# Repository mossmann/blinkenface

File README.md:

# blinkenface
party glasses with blinky lights

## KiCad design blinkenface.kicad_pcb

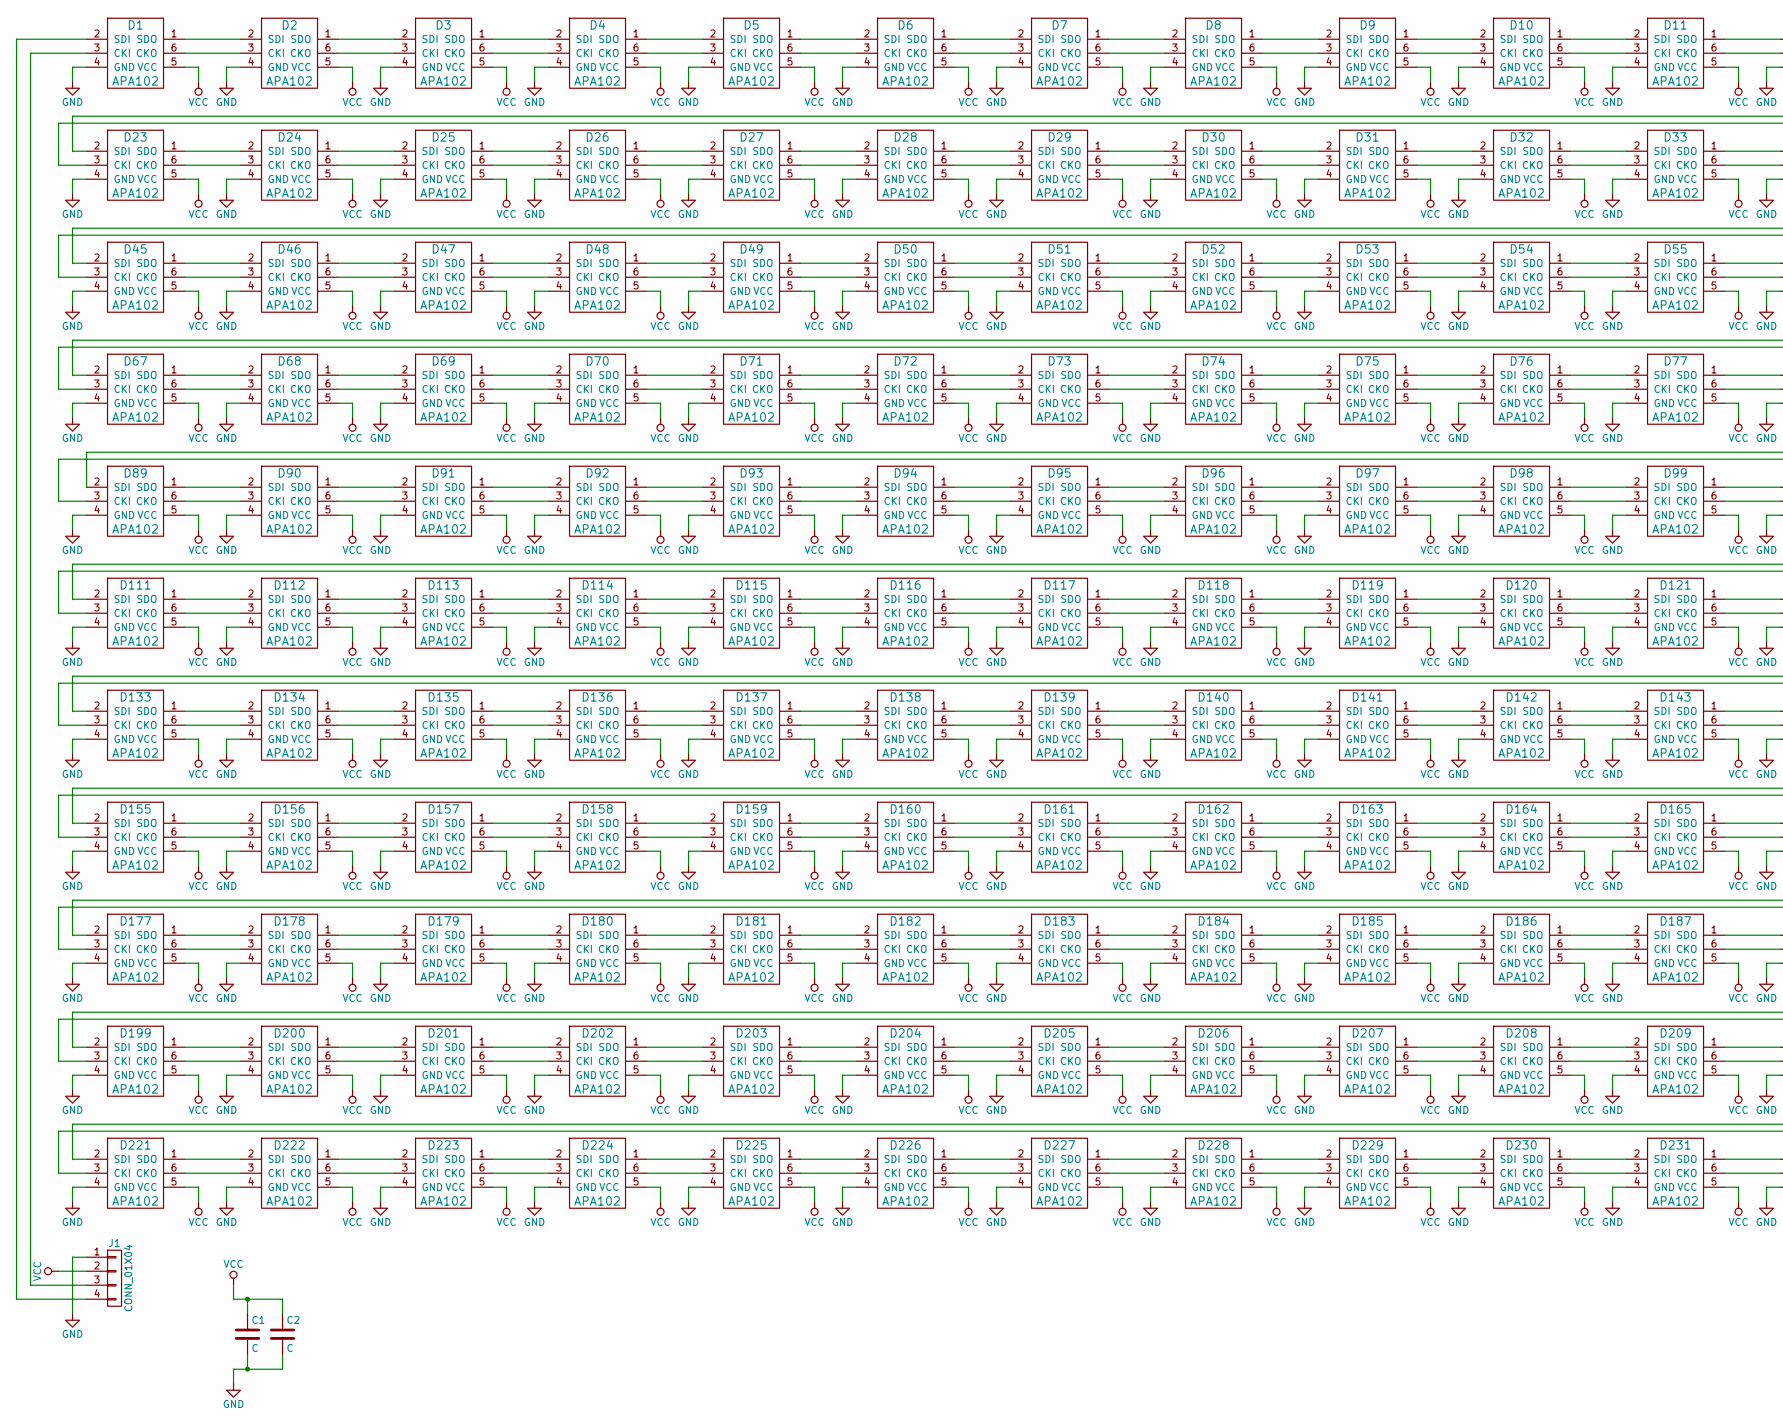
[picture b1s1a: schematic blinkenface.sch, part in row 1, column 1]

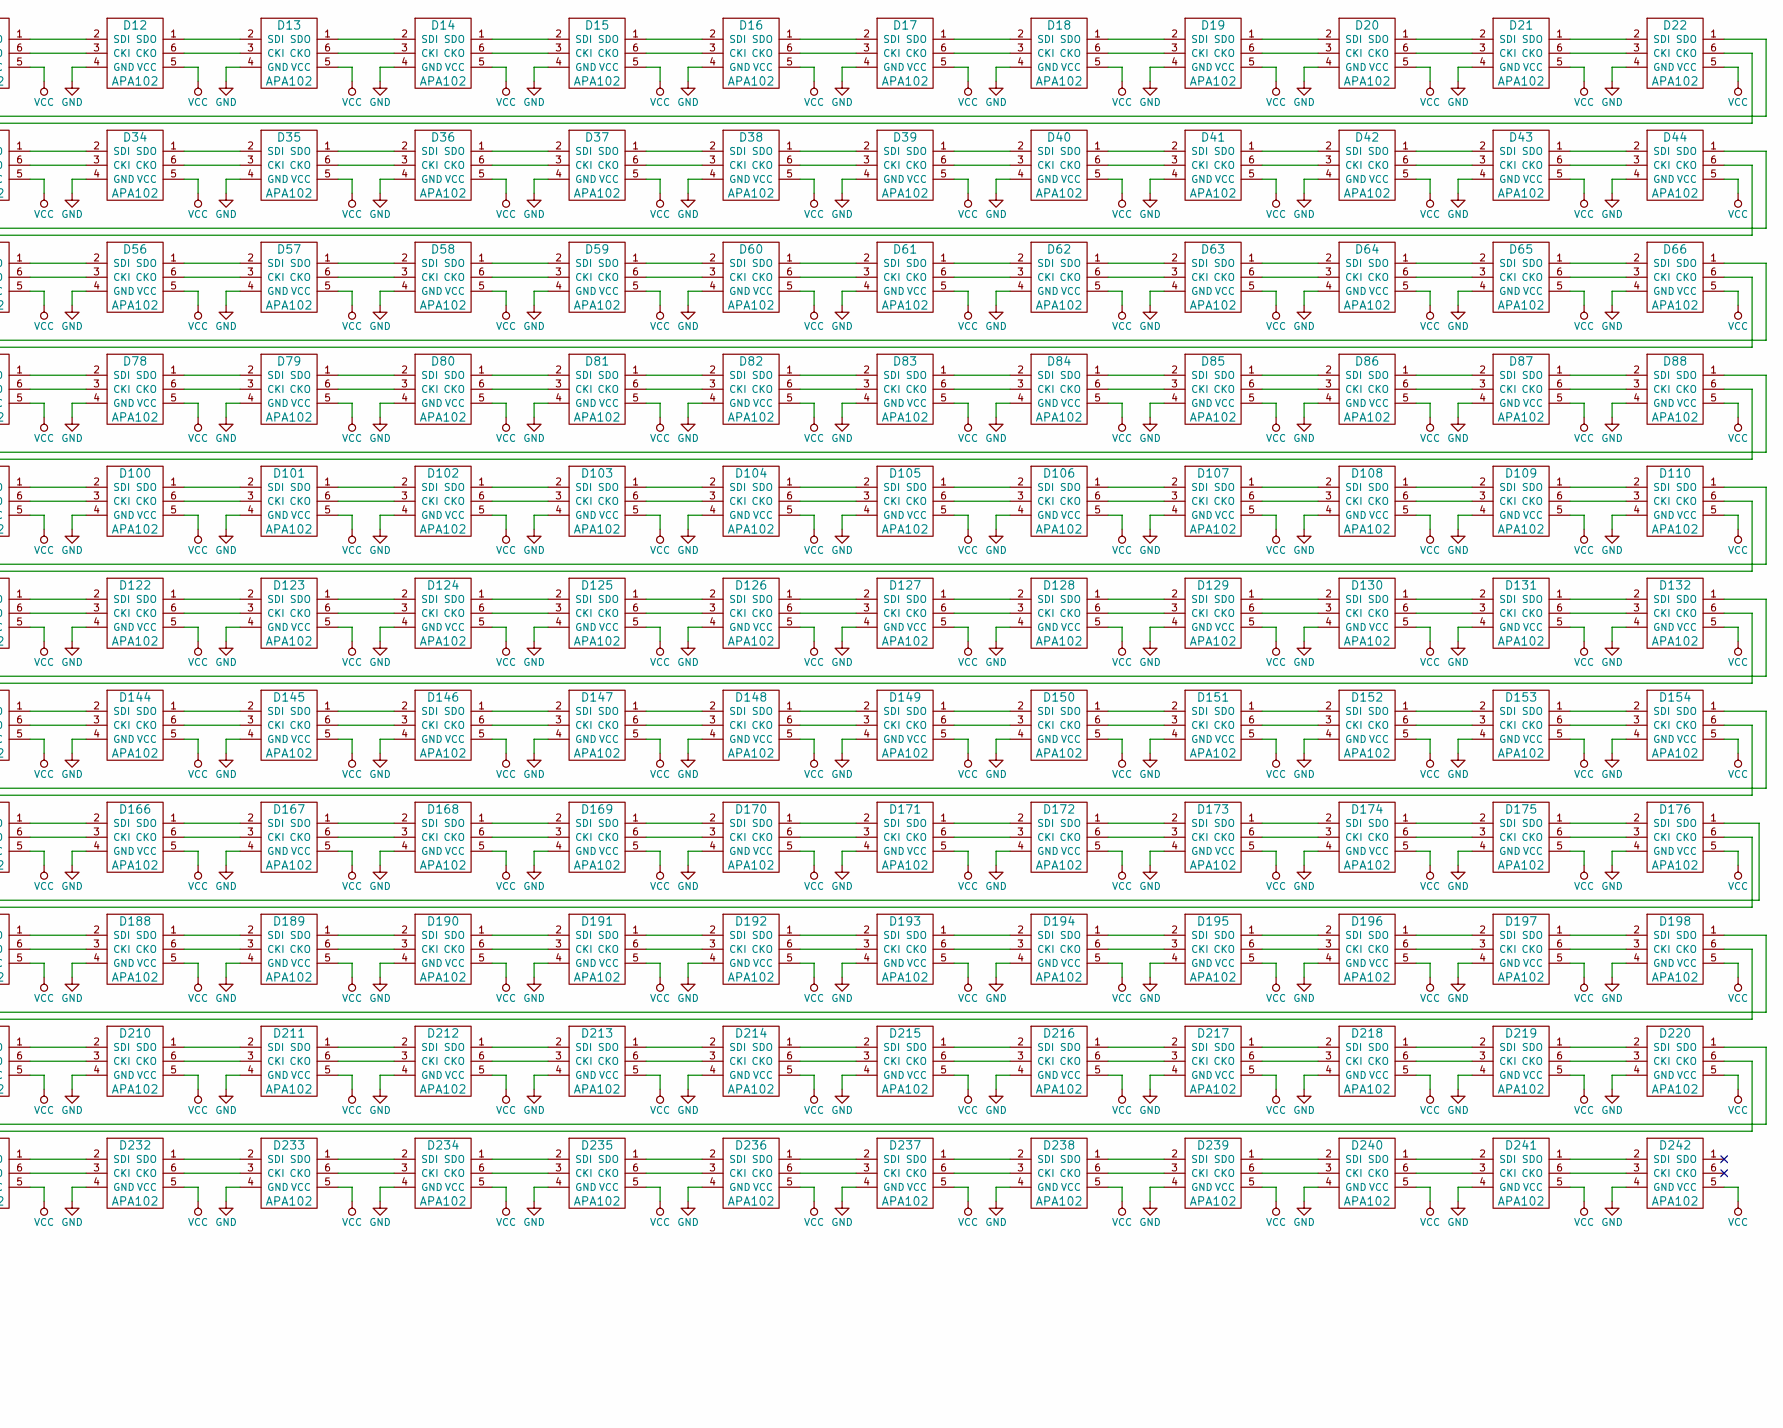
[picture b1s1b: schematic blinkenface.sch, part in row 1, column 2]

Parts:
C1: C; 0805
C2: C; 0603
D1, D2, D3, D4, D5, D6, D7, D8, D9, D10, D11, D12, D13, D14, D15, D16, D17, D18, D19, D20, D21, D22, D23, D24, D25, D26, D27, D28, D29, D30, D31, D32, D33, D34, D35, D36, D37, D38, D39, D40, D41, D42, D43, D44, D45, D46, D47, D48, D49, D50, D51, D52, D53, D54, D55, D56, D57, D58, D59, D60, D61, D62, D63, D64, D65, D66, D67, D68, D69, D70, D71, D72, D73, D74, D75, D76, D77, D78, D79, D80, D81, D82, D83, D84, D85, D86, D87, D88, D89, D90, D91, D92, D93, D94, D95, D96, D97, D98, D99, D100, D101, D102, D103, D104, D105, D106, D107, D108, D109, D110, D111, D112, D113, D114, D115, D116, D117, D118, D119, D120, D121, D122, D123, D124, D125, D126, D127, D128, D129, D130, D131, D132, D133, D134, D135, D136, D137, D138, D139, D140, D141, D142, D143, D144, D145, D146, D147, D148, D149, D150, D151, D152, D153, D154, D155, D156, D157, D158, D159, D160, D161, D162, D163, D164, D165, D166, D167, D168, D169, D170, D171, D172, D173, D174, D175, D176, D177, D178, D179, D180, D181, D182, D183, D184, D185, D186, D187, D188, D189, D190, D191, D192, D193, D194, D195, D196, D197, D198, D199, D200, D201, D202, D203, D204, D205, D206, D207, D208, D209, D210, D211, D212, D213, D214, D215, D216, D217, D218, D219, D220, D221, D222, D223, D224, D225, D226, D227, D228, D229, D230, D231, D232, D233, D234, D235, D236, D237, D238, D239, D240, D241, D242: APA102; APA102-2020
J1: CONN_01X04; HEADER-1x4

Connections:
GND: C1.2, C2.2, D1.4 (GND), D2.4 (GND), D3.4 (GND), D4.4 (GND), D5.4 (GND), D6.4 (GND), D7.4 (GND), D8.4 (GND), D9.4 (GND), D10.4 (GND), D11.4 (GND), D12.4 (GND), D13.4 (GND), D14.4 (GND), D15.4 (GND), D16.4 (GND), D17.4 (GND), D18.4 (GND), D19.4 (GND), D20.4 (GND), D21.4 (GND), D22.4 (GND), D23.4 (GND), D24.4 (GND), D25.4 (GND), D26.4 (GND), D27.4 (GND), D28.4 (GND), D29.4 (GND), D30.4 (GND), D31.4 (GND), D32.4 (GND), D33.4 (GND), D34.4 (GND), D35.4 (GND), D36.4 (GND), D37.4 (GND), D38.4 (GND), D39.4 (GND), D40.4 (GND), D41.4 (GND), D42.4 (GND), D43.4 (GND), D44.4 (GND), D45.4 (GND), D46.4 (GND), D47.4 (GND), D48.4 (GND), D49.4 (GND), D50.4 (GND), D51.4 (GND), D52.4 (GND), D53.4 (GND), D54.4 (GND), D55.4 (GND), D56.4 (GND), D57.4 (GND), D58.4 (GND), D59.4 (GND), D60.4 (GND), D61.4 (GND), D62.4 (GND), D63.4 (GND), D64.4 (GND), D65.4 (GND), D66.4 (GND), D67.4 (GND), D68.4 (GND), D69.4 (GND), D70.4 (GND), D71.4 (GND), D72.4 (GND), D73.4 (GND), D74.4 (GND), D75.4 (GND), D76.4 (GND), D77.4 (GND), D78.4 (GND), D79.4 (GND), D80.4 (GND), D81.4 (GND), D82.4 (GND), D83.4 (GND), D84.4 (GND), D85.4 (GND), D86.4 (GND), D87.4 (GND), D88.4 (GND), D89.4 (GND), D90.4 (GND), D91.4 (GND), D92.4 (GND), D93.4 (GND), D94.4 (GND), D95.4 (GND), D96.4 (GND), D97.4 (GND), D98.4 (GND), D99.4 (GND), D100.4 (GND), D101.4 (GND), D102.4 (GND), D103.4 (GND), D104.4 (GND), D105.4 (GND), D106.4 (GND), D107.4 (GND), D108.4 (GND), D109.4 (GND), D110.4 (GND), D111.4 (GND), D112.4 (GND), D113.4 (GND), D114.4 (GND), D115.4 (GND), D116.4 (GND), D117.4 (GND), D118.4 (GND), D119.4 (GND), D120.4 (GND), D121.4 (GND), D122.4 (GND), D123.4 (GND), D124.4 (GND), D125.4 (GND), D126.4 (GND), D127.4 (GND), D128.4 (GND), D129.4 (GND), D130.4 (GND), D131.4 (GND), D132.4 (GND), D133.4 (GND), D134.4 (GND), D135.4 (GND), D136.4 (GND), D137.4 (GND), D138.4 (GND), D139.4 (GND), D140.4 (GND), D141.4 (GND), D142.4 (GND), D143.4 (GND), D144.4 (GND), D145.4 (GND), D146.4 (GND), D147.4 (GND), D148.4 (GND), D149.4 (GND), D150.4 (GND), D151.4 (GND), D152.4 (GND), D153.4 (GND), D154.4 (GND), D155.4 (GND), D156.4 (GND), D157.4 (GND), D158.4 (GND), D159.4 (GND), D160.4 (GND), D161.4 (GND), D162.4 (GND), D163.4 (GND), D164.4 (GND), D165.4 (GND), D166.4 (GND), D167.4 (GND), D168.4 (GND), D169.4 (GND), D170.4 (GND), D171.4 (GND), D172.4 (GND), D173.4 (GND), D174.4 (GND), D175.4 (GND), D176.4 (GND), D177.4 (GND), D178.4 (GND), D179.4 (GND), D180.4 (GND), D181.4 (GND), D182.4 (GND), D183.4 (GND), D184.4 (GND), D185.4 (GND), D186.4 (GND), D187.4 (GND), D188.4 (GND), D189.4 (GND), D190.4 (GND), D191.4 (GND), D192.4 (GND), D193.4 (GND), D194.4 (GND), D195.4 (GND), D196.4 (GND), D197.4 (GND), D198.4 (GND), D199.4 (GND), D200.4 (GND), D201.4 (GND), D202.4 (GND), D203.4 (GND), D204.4 (GND), D205.4 (GND), D206.4 (GND), D207.4 (GND), D208.4 (GND), D209.4 (GND), D210.4 (GND), D211.4 (GND), D212.4 (GND), D213.4 (GND), D214.4 (GND), D215.4 (GND), D216.4 (GND), D217.4 (GND), D218.4 (GND), D219.4 (GND), D220.4 (GND), D221.4 (GND), D222.4 (GND), D223.4 (GND), D224.4 (GND), D225.4 (GND), D226.4 (GND), D227.4 (GND), D228.4 (GND), D229.4 (GND), D230.4 (GND), D231.4 (GND), D232.4 (GND), D233.4 (GND), D234.4 (GND), D235.4 (GND), D236.4 (GND), D237.4 (GND), D238.4 (GND), D239.4 (GND), D240.4 (GND), D241.4 (GND), D242.4 (GND), J1.1
unnamed: D1.1 (SDO), D2.2 (SDI)
unnamed: D1.2 (SDI), J1.4
unnamed: D1.3 (CKI), J1.3
unnamed: D1.6 (CKO), D2.3 (CKI)
unnamed: D2.1 (SDO), D3.2 (SDI)
unnamed: D2.6 (CKO), D3.3 (CKI)
unnamed: D3.1 (SDO), D4.2 (SDI)
unnamed: D3.6 (CKO), D4.3 (CKI)
unnamed: D4.1 (SDO), D5.2 (SDI)
unnamed: D4.6 (CKO), D5.3 (CKI)
unnamed: D5.1 (SDO), D6.2 (SDI)
unnamed: D5.6 (CKO), D6.3 (CKI)
unnamed: D6.1 (SDO), D7.2 (SDI)
unnamed: D6.6 (CKO), D7.3 (CKI)
unnamed: D7.1 (SDO), D8.2 (SDI)
unnamed: D7.6 (CKO), D8.3 (CKI)
unnamed: D8.1 (SDO), D9.2 (SDI)
unnamed: D8.6 (CKO), D9.3 (CKI)
unnamed: D10.1 (SDO), D11.2 (SDI)
unnamed: D9.1 (SDO), D10.2 (SDI)
unnamed: D9.6 (CKO), D10.3 (CKI)
unnamed: D10.6 (CKO), D11.3 (CKI)
unnamed: D11.1 (SDO), D12.2 (SDI)
unnamed: D11.6 (CKO), D12.3 (CKI)
unnamed: D12.1 (SDO), D13.2 (SDI)
unnamed: D12.6 (CKO), D13.3 (CKI)
unnamed: D13.1 (SDO), D14.2 (SDI)
unnamed: D13.6 (CKO), D14.3 (CKI)
unnamed: D14.1 (SDO), D15.2 (SDI)
unnamed: D14.6 (CKO), D15.3 (CKI)
unnamed: D15.1 (SDO), D16.2 (SDI)
unnamed: D15.6 (CKO), D16.3 (CKI)
unnamed: D16.1 (SDO), D17.2 (SDI)
unnamed: D16.6 (CKO), D17.3 (CKI)
unnamed: D17.1 (SDO), D18.2 (SDI)
unnamed: D17.6 (CKO), D18.3 (CKI)
unnamed: D18.1 (SDO), D19.2 (SDI)
unnamed: D18.6 (CKO), D19.3 (CKI)
unnamed: D19.1 (SDO), D20.2 (SDI)
unnamed: D19.6 (CKO), D20.3 (CKI)
unnamed: D20.1 (SDO), D21.2 (SDI)
unnamed: D20.6 (CKO), D21.3 (CKI)
unnamed: D21.1 (SDO), D22.2 (SDI)
unnamed: D21.6 (CKO), D22.3 (CKI)
unnamed: D22.1 (SDO), D23.2 (SDI)
unnamed: D22.6 (CKO), D23.3 (CKI)
unnamed: D23.1 (SDO), D24.2 (SDI)
unnamed: D23.6 (CKO), D24.3 (CKI)
unnamed: D24.1 (SDO), D25.2 (SDI)
unnamed: D24.6 (CKO), D25.3 (CKI)
unnamed: D25.1 (SDO), D26.2 (SDI)
unnamed: D25.6 (CKO), D26.3 (CKI)
unnamed: D26.1 (SDO), D27.2 (SDI)
unnamed: D26.6 (CKO), D27.3 (CKI)
unnamed: D27.1 (SDO), D28.2 (SDI)
unnamed: D27.6 (CKO), D28.3 (CKI)
unnamed: D28.1 (SDO), D29.2 (SDI)
unnamed: D28.6 (CKO), D29.3 (CKI)
unnamed: D29.1 (SDO), D30.2 (SDI)
unnamed: D29.6 (CKO), D30.3 (CKI)
unnamed: D30.1 (SDO), D31.2 (SDI)
unnamed: D30.6 (CKO), D31.3 (CKI)
unnamed: D31.1 (SDO), D32.2 (SDI)
unnamed: D31.6 (CKO), D32.3 (CKI)
unnamed: D32.1 (SDO), D33.2 (SDI)
unnamed: D32.6 (CKO), D33.3 (CKI)
unnamed: D33.1 (SDO), D34.2 (SDI)
unnamed: D33.6 (CKO), D34.3 (CKI)
unnamed: D34.1 (SDO), D35.2 (SDI)
unnamed: D34.6 (CKO), D35.3 (CKI)
unnamed: D35.1 (SDO), D36.2 (SDI)
unnamed: D35.6 (CKO), D36.3 (CKI)
unnamed: D36.1 (SDO), D37.2 (SDI)
unnamed: D36.6 (CKO), D37.3 (CKI)
unnamed: D37.1 (SDO), D38.2 (SDI)
unnamed: D37.6 (CKO), D38.3 (CKI)
unnamed: D38.1 (SDO), D39.2 (SDI)
unnamed: D38.6 (CKO), D39.3 (CKI)
unnamed: D39.1 (SDO), D40.2 (SDI)
unnamed: D39.6 (CKO), D40.3 (CKI)
unnamed: D40.1 (SDO), D41.2 (SDI)
unnamed: D40.6 (CKO), D41.3 (CKI)
unnamed: D41.1 (SDO), D42.2 (SDI)
unnamed: D41.6 (CKO), D42.3 (CKI)
unnamed: D42.1 (SDO), D43.2 (SDI)
unnamed: D42.6 (CKO), D43.3 (CKI)
unnamed: D43.1 (SDO), D44.2 (SDI)
unnamed: D43.6 (CKO), D44.3 (CKI)
unnamed: D44.1 (SDO), D45.2 (SDI)
unnamed: D44.6 (CKO), D45.3 (CKI)
unnamed: D45.1 (SDO), D46.2 (SDI)
unnamed: D45.6 (CKO), D46.3 (CKI)
unnamed: D46.1 (SDO), D47.2 (SDI)
unnamed: D46.6 (CKO), D47.3 (CKI)
unnamed: D47.1 (SDO), D48.2 (SDI)
unnamed: D47.6 (CKO), D48.3 (CKI)
unnamed: D48.1 (SDO), D49.2 (SDI)
unnamed: D48.6 (CKO), D49.3 (CKI)
unnamed: D49.1 (SDO), D50.2 (SDI)
unnamed: D49.6 (CKO), D50.3 (CKI)
unnamed: D50.1 (SDO), D51.2 (SDI)
unnamed: D50.6 (CKO), D51.3 (CKI)
unnamed: D51.1 (SDO), D52.2 (SDI)
unnamed: D51.6 (CKO), D52.3 (CKI)
unnamed: D52.1 (SDO), D53.2 (SDI)
unnamed: D52.6 (CKO), D53.3 (CKI)
unnamed: D53.1 (SDO), D54.2 (SDI)
unnamed: D53.6 (CKO), D54.3 (CKI)
unnamed: D54.1 (SDO), D55.2 (SDI)
unnamed: D54.6 (CKO), D55.3 (CKI)
unnamed: D55.1 (SDO), D56.2 (SDI)
unnamed: D55.6 (CKO), D56.3 (CKI)
unnamed: D56.1 (SDO), D57.2 (SDI)
unnamed: D56.6 (CKO), D57.3 (CKI)
unnamed: D57.1 (SDO), D58.2 (SDI)
unnamed: D57.6 (CKO), D58.3 (CKI)
unnamed: D58.1 (SDO), D59.2 (SDI)
unnamed: D58.6 (CKO), D59.3 (CKI)
unnamed: D59.1 (SDO), D60.2 (SDI)
unnamed: D59.6 (CKO), D60.3 (CKI)
unnamed: D60.1 (SDO), D61.2 (SDI)
unnamed: D60.6 (CKO), D61.3 (CKI)
unnamed: D61.1 (SDO), D62.2 (SDI)
unnamed: D61.6 (CKO), D62.3 (CKI)
unnamed: D62.1 (SDO), D63.2 (SDI)
unnamed: D62.6 (CKO), D63.3 (CKI)
unnamed: D63.1 (SDO), D64.2 (SDI)
unnamed: D63.6 (CKO), D64.3 (CKI)
unnamed: D64.1 (SDO), D65.2 (SDI)
unnamed: D64.6 (CKO), D65.3 (CKI)
unnamed: D65.1 (SDO), D66.2 (SDI)
unnamed: D65.6 (CKO), D66.3 (CKI)
unnamed: D66.1 (SDO), D67.2 (SDI)
unnamed: D66.6 (CKO), D67.3 (CKI)
unnamed: D67.1 (SDO), D68.2 (SDI)
unnamed: D67.6 (CKO), D68.3 (CKI)
unnamed: D68.1 (SDO), D69.2 (SDI)
unnamed: D68.6 (CKO), D69.3 (CKI)
unnamed: D69.1 (SDO), D70.2 (SDI)
unnamed: D69.6 (CKO), D70.3 (CKI)
unnamed: D70.1 (SDO), D71.2 (SDI)
unnamed: D70.6 (CKO), D71.3 (CKI)
unnamed: D71.1 (SDO), D72.2 (SDI)
unnamed: D71.6 (CKO), D72.3 (CKI)
unnamed: D72.1 (SDO), D73.2 (SDI)
unnamed: D72.6 (CKO), D73.3 (CKI)
unnamed: D73.1 (SDO), D74.2 (SDI)
unnamed: D73.6 (CKO), D74.3 (CKI)
unnamed: D74.1 (SDO), D75.2 (SDI)
unnamed: D74.6 (CKO), D75.3 (CKI)
unnamed: D75.1 (SDO), D76.2 (SDI)
unnamed: D75.6 (CKO), D76.3 (CKI)
unnamed: D76.1 (SDO), D77.2 (SDI)
unnamed: D76.6 (CKO), D77.3 (CKI)
unnamed: D77.1 (SDO), D78.2 (SDI)
unnamed: D77.6 (CKO), D78.3 (CKI)
unnamed: D78.1 (SDO), D79.2 (SDI)
unnamed: D78.6 (CKO), D79.3 (CKI)
unnamed: D79.1 (SDO), D80.2 (SDI)
unnamed: D79.6 (CKO), D80.3 (CKI)
unnamed: D80.1 (SDO), D81.2 (SDI)
unnamed: D80.6 (CKO), D81.3 (CKI)
unnamed: D81.1 (SDO), D82.2 (SDI)
unnamed: D81.6 (CKO), D82.3 (CKI)
unnamed: D82.1 (SDO), D83.2 (SDI)
unnamed: D82.6 (CKO), D83.3 (CKI)
unnamed: D83.1 (SDO), D84.2 (SDI)
unnamed: D83.6 (CKO), D84.3 (CKI)
unnamed: D84.1 (SDO), D85.2 (SDI)
unnamed: D84.6 (CKO), D85.3 (CKI)
unnamed: D85.1 (SDO), D86.2 (SDI)
unnamed: D85.6 (CKO), D86.3 (CKI)
unnamed: D86.1 (SDO), D87.2 (SDI)
unnamed: D86.6 (CKO), D87.3 (CKI)
unnamed: D87.1 (SDO), D88.2 (SDI)
unnamed: D87.6 (CKO), D88.3 (CKI)
unnamed: D88.1 (SDO), D89.2 (SDI)
unnamed: D88.6 (CKO), D89.3 (CKI)
unnamed: D89.1 (SDO), D90.2 (SDI)
unnamed: D89.6 (CKO), D90.3 (CKI)
unnamed: D90.1 (SDO), D91.2 (SDI)
unnamed: D90.6 (CKO), D91.3 (CKI)
unnamed: D91.1 (SDO), D92.2 (SDI)
unnamed: D91.6 (CKO), D92.3 (CKI)
unnamed: D92.1 (SDO), D93.2 (SDI)
unnamed: D92.6 (CKO), D93.3 (CKI)
unnamed: D93.1 (SDO), D94.2 (SDI)
unnamed: D93.6 (CKO), D94.3 (CKI)
unnamed: D94.1 (SDO), D95.2 (SDI)
unnamed: D94.6 (CKO), D95.3 (CKI)
unnamed: D95.1 (SDO), D96.2 (SDI)
unnamed: D95.6 (CKO), D96.3 (CKI)
unnamed: D96.1 (SDO), D97.2 (SDI)
unnamed: D96.6 (CKO), D97.3 (CKI)
unnamed: D97.1 (SDO), D98.2 (SDI)
unnamed: D97.6 (CKO), D98.3 (CKI)
unnamed: D98.1 (SDO), D99.2 (SDI)
unnamed: D98.6 (CKO), D99.3 (CKI)
unnamed: D100.1 (SDO), D101.2 (SDI)
unnamed: D99.1 (SDO), D100.2 (SDI)
unnamed: D99.6 (CKO), D100.3 (CKI)
unnamed: D100.6 (CKO), D101.3 (CKI)
unnamed: D101.1 (SDO), D102.2 (SDI)
unnamed: D101.6 (CKO), D102.3 (CKI)
unnamed: D102.1 (SDO), D103.2 (SDI)
unnamed: D102.6 (CKO), D103.3 (CKI)
unnamed: D103.1 (SDO), D104.2 (SDI)
unnamed: D103.6 (CKO), D104.3 (CKI)
unnamed: D104.1 (SDO), D105.2 (SDI)
unnamed: D104.6 (CKO), D105.3 (CKI)
unnamed: D105.1 (SDO), D106.2 (SDI)
unnamed: D105.6 (CKO), D106.3 (CKI)
unnamed: D106.1 (SDO), D107.2 (SDI)
unnamed: D106.6 (CKO), D107.3 (CKI)
unnamed: D107.1 (SDO), D108.2 (SDI)
unnamed: D107.6 (CKO), D108.3 (CKI)
unnamed: D108.1 (SDO), D109.2 (SDI)
unnamed: D108.6 (CKO), D109.3 (CKI)
unnamed: D109.1 (SDO), D110.2 (SDI)
unnamed: D109.6 (CKO), D110.3 (CKI)
unnamed: D110.1 (SDO), D111.2 (SDI)
unnamed: D110.6 (CKO), D111.3 (CKI)
unnamed: D111.1 (SDO), D112.2 (SDI)
unnamed: D111.6 (CKO), D112.3 (CKI)
unnamed: D112.1 (SDO), D113.2 (SDI)
unnamed: D112.6 (CKO), D113.3 (CKI)
unnamed: D113.1 (SDO), D114.2 (SDI)
unnamed: D113.6 (CKO), D114.3 (CKI)
unnamed: D114.1 (SDO), D115.2 (SDI)
unnamed: D114.6 (CKO), D115.3 (CKI)
unnamed: D115.1 (SDO), D116.2 (SDI)
unnamed: D115.6 (CKO), D116.3 (CKI)
unnamed: D116.1 (SDO), D117.2 (SDI)
unnamed: D116.6 (CKO), D117.3 (CKI)
unnamed: D117.1 (SDO), D118.2 (SDI)
unnamed: D117.6 (CKO), D118.3 (CKI)
unnamed: D118.1 (SDO), D119.2 (SDI)
unnamed: D118.6 (CKO), D119.3 (CKI)
unnamed: D119.1 (SDO), D120.2 (SDI)
unnamed: D119.6 (CKO), D120.3 (CKI)
unnamed: D120.1 (SDO), D121.2 (SDI)
unnamed: D120.6 (CKO), D121.3 (CKI)
unnamed: D121.1 (SDO), D122.2 (SDI)
unnamed: D121.6 (CKO), D122.3 (CKI)
unnamed: D122.1 (SDO), D123.2 (SDI)
unnamed: D122.6 (CKO), D123.3 (CKI)
unnamed: D123.1 (SDO), D124.2 (SDI)
unnamed: D123.6 (CKO), D124.3 (CKI)
unnamed: D124.1 (SDO), D125.2 (SDI)
unnamed: D124.6 (CKO), D125.3 (CKI)
unnamed: D125.1 (SDO), D126.2 (SDI)
unnamed: D125.6 (CKO), D126.3 (CKI)
unnamed: D126.1 (SDO), D127.2 (SDI)
unnamed: D126.6 (CKO), D127.3 (CKI)
unnamed: D127.1 (SDO), D128.2 (SDI)
unnamed: D127.6 (CKO), D128.3 (CKI)
unnamed: D128.1 (SDO), D129.2 (SDI)
unnamed: D128.6 (CKO), D129.3 (CKI)
unnamed: D129.1 (SDO), D130.2 (SDI)
unnamed: D129.6 (CKO), D130.3 (CKI)
unnamed: D130.1 (SDO), D131.2 (SDI)
unnamed: D130.6 (CKO), D131.3 (CKI)
unnamed: D131.1 (SDO), D132.2 (SDI)
unnamed: D131.6 (CKO), D132.3 (CKI)
unnamed: D132.1 (SDO), D133.2 (SDI)
unnamed: D132.6 (CKO), D133.3 (CKI)
unnamed: D133.1 (SDO), D134.2 (SDI)
unnamed: D133.6 (CKO), D134.3 (CKI)
unnamed: D134.1 (SDO), D135.2 (SDI)
unnamed: D134.6 (CKO), D135.3 (CKI)
unnamed: D135.1 (SDO), D136.2 (SDI)
unnamed: D135.6 (CKO), D136.3 (CKI)
unnamed: D136.1 (SDO), D137.2 (SDI)
unnamed: D136.6 (CKO), D137.3 (CKI)
unnamed: D137.1 (SDO), D138.2 (SDI)
unnamed: D137.6 (CKO), D138.3 (CKI)
unnamed: D138.1 (SDO), D139.2 (SDI)
unnamed: D138.6 (CKO), D139.3 (CKI)
unnamed: D139.1 (SDO), D140.2 (SDI)
unnamed: D139.6 (CKO), D140.3 (CKI)
unnamed: D140.1 (SDO), D141.2 (SDI)
unnamed: D140.6 (CKO), D141.3 (CKI)
unnamed: D141.1 (SDO), D142.2 (SDI)
unnamed: D141.6 (CKO), D142.3 (CKI)
unnamed: D142.1 (SDO), D143.2 (SDI)
unnamed: D142.6 (CKO), D143.3 (CKI)
unnamed: D143.1 (SDO), D144.2 (SDI)
unnamed: D143.6 (CKO), D144.3 (CKI)
unnamed: D144.1 (SDO), D145.2 (SDI)
unnamed: D144.6 (CKO), D145.3 (CKI)
unnamed: D145.1 (SDO), D146.2 (SDI)
unnamed: D145.6 (CKO), D146.3 (CKI)
unnamed: D146.1 (SDO), D147.2 (SDI)
unnamed: D146.6 (CKO), D147.3 (CKI)
unnamed: D147.1 (SDO), D148.2 (SDI)
unnamed: D147.6 (CKO), D148.3 (CKI)
unnamed: D148.1 (SDO), D149.2 (SDI)
unnamed: D148.6 (CKO), D149.3 (CKI)
unnamed: D149.1 (SDO), D150.2 (SDI)
unnamed: D149.6 (CKO), D150.3 (CKI)
unnamed: D150.1 (SDO), D151.2 (SDI)
unnamed: D150.6 (CKO), D151.3 (CKI)
unnamed: D151.1 (SDO), D152.2 (SDI)
unnamed: D151.6 (CKO), D152.3 (CKI)
unnamed: D152.1 (SDO), D153.2 (SDI)
unnamed: D152.6 (CKO), D153.3 (CKI)
unnamed: D153.1 (SDO), D154.2 (SDI)
unnamed: D153.6 (CKO), D154.3 (CKI)
unnamed: D154.1 (SDO), D155.2 (SDI)
unnamed: D154.6 (CKO), D155.3 (CKI)
unnamed: D155.1 (SDO), D156.2 (SDI)
unnamed: D155.6 (CKO), D156.3 (CKI)
unnamed: D156.1 (SDO), D157.2 (SDI)
unnamed: D156.6 (CKO), D157.3 (CKI)
unnamed: D157.1 (SDO), D158.2 (SDI)
unnamed: D157.6 (CKO), D158.3 (CKI)
unnamed: D158.1 (SDO), D159.2 (SDI)
unnamed: D158.6 (CKO), D159.3 (CKI)
unnamed: D159.1 (SDO), D160.2 (SDI)
unnamed: D159.6 (CKO), D160.3 (CKI)
unnamed: D160.1 (SDO), D161.2 (SDI)
unnamed: D160.6 (CKO), D161.3 (CKI)
unnamed: D161.1 (SDO), D162.2 (SDI)
unnamed: D161.6 (CKO), D162.3 (CKI)
unnamed: D162.1 (SDO), D163.2 (SDI)
unnamed: D162.6 (CKO), D163.3 (CKI)
unnamed: D163.1 (SDO), D164.2 (SDI)
unnamed: D163.6 (CKO), D164.3 (CKI)
unnamed: D164.1 (SDO), D165.2 (SDI)
unnamed: D164.6 (CKO), D165.3 (CKI)
unnamed: D165.1 (SDO), D166.2 (SDI)
unnamed: D165.6 (CKO), D166.3 (CKI)
unnamed: D166.1 (SDO), D167.2 (SDI)
unnamed: D166.6 (CKO), D167.3 (CKI)
unnamed: D167.1 (SDO), D168.2 (SDI)
unnamed: D167.6 (CKO), D168.3 (CKI)
unnamed: D168.1 (SDO), D169.2 (SDI)
unnamed: D168.6 (CKO), D169.3 (CKI)
unnamed: D169.1 (SDO), D170.2 (SDI)
unnamed: D169.6 (CKO), D170.3 (CKI)
unnamed: D170.1 (SDO), D171.2 (SDI)
unnamed: D170.6 (CKO), D171.3 (CKI)
unnamed: D171.1 (SDO), D172.2 (SDI)
unnamed: D171.6 (CKO), D172.3 (CKI)
unnamed: D172.1 (SDO), D173.2 (SDI)
unnamed: D172.6 (CKO), D173.3 (CKI)
unnamed: D173.1 (SDO), D174.2 (SDI)
unnamed: D173.6 (CKO), D174.3 (CKI)
unnamed: D174.1 (SDO), D175.2 (SDI)
unnamed: D174.6 (CKO), D175.3 (CKI)
unnamed: D175.1 (SDO), D176.2 (SDI)
unnamed: D175.6 (CKO), D176.3 (CKI)
unnamed: D176.1 (SDO), D177.2 (SDI)
unnamed: D176.6 (CKO), D177.3 (CKI)
unnamed: D177.1 (SDO), D178.2 (SDI)
unnamed: D177.6 (CKO), D178.3 (CKI)
unnamed: D178.1 (SDO), D179.2 (SDI)
unnamed: D178.6 (CKO), D179.3 (CKI)
unnamed: D179.1 (SDO), D180.2 (SDI)
unnamed: D179.6 (CKO), D180.3 (CKI)
unnamed: D180.1 (SDO), D181.2 (SDI)
unnamed: D180.6 (CKO), D181.3 (CKI)
unnamed: D181.1 (SDO), D182.2 (SDI)
unnamed: D181.6 (CKO), D182.3 (CKI)
unnamed: D182.1 (SDO), D183.2 (SDI)
unnamed: D182.6 (CKO), D183.3 (CKI)
unnamed: D183.1 (SDO), D184.2 (SDI)
unnamed: D183.6 (CKO), D184.3 (CKI)
unnamed: D184.1 (SDO), D185.2 (SDI)
unnamed: D184.6 (CKO), D185.3 (CKI)
unnamed: D185.1 (SDO), D186.2 (SDI)
unnamed: D185.6 (CKO), D186.3 (CKI)
unnamed: D186.1 (SDO), D187.2 (SDI)
unnamed: D186.6 (CKO), D187.3 (CKI)
unnamed: D187.1 (SDO), D188.2 (SDI)
unnamed: D187.6 (CKO), D188.3 (CKI)
unnamed: D188.1 (SDO), D189.2 (SDI)
unnamed: D188.6 (CKO), D189.3 (CKI)
unnamed: D189.1 (SDO), D190.2 (SDI)
unnamed: D189.6 (CKO), D190.3 (CKI)
unnamed: D190.1 (SDO), D191.2 (SDI)
unnamed: D190.6 (CKO), D191.3 (CKI)
unnamed: D191.1 (SDO), D192.2 (SDI)
unnamed: D191.6 (CKO), D192.3 (CKI)
unnamed: D192.1 (SDO), D193.2 (SDI)
unnamed: D192.6 (CKO), D193.3 (CKI)
unnamed: D193.1 (SDO), D194.2 (SDI)
unnamed: D193.6 (CKO), D194.3 (CKI)
unnamed: D194.1 (SDO), D195.2 (SDI)
unnamed: D194.6 (CKO), D195.3 (CKI)
unnamed: D195.1 (SDO), D196.2 (SDI)
unnamed: D195.6 (CKO), D196.3 (CKI)
unnamed: D196.1 (SDO), D197.2 (SDI)
unnamed: D196.6 (CKO), D197.3 (CKI)
unnamed: D197.1 (SDO), D198.2 (SDI)
unnamed: D197.6 (CKO), D198.3 (CKI)
unnamed: D198.1 (SDO), D199.2 (SDI)
unnamed: D198.6 (CKO), D199.3 (CKI)
unnamed: D199.1 (SDO), D200.2 (SDI)
unnamed: D199.6 (CKO), D200.3 (CKI)
unnamed: D200.1 (SDO), D201.2 (SDI)
unnamed: D200.6 (CKO), D201.3 (CKI)
unnamed: D201.1 (SDO), D202.2 (SDI)
unnamed: D201.6 (CKO), D202.3 (CKI)
unnamed: D202.1 (SDO), D203.2 (SDI)
unnamed: D202.6 (CKO), D203.3 (CKI)
unnamed: D203.1 (SDO), D204.2 (SDI)
unnamed: D203.6 (CKO), D204.3 (CKI)
unnamed: D204.1 (SDO), D205.2 (SDI)
unnamed: D204.6 (CKO), D205.3 (CKI)
unnamed: D205.1 (SDO), D206.2 (SDI)
unnamed: D205.6 (CKO), D206.3 (CKI)
unnamed: D206.1 (SDO), D207.2 (SDI)
unnamed: D206.6 (CKO), D207.3 (CKI)
unnamed: D207.1 (SDO), D208.2 (SDI)
unnamed: D207.6 (CKO), D208.3 (CKI)
unnamed: D208.1 (SDO), D209.2 (SDI)
unnamed: D208.6 (CKO), D209.3 (CKI)
unnamed: D209.1 (SDO), D210.2 (SDI)
unnamed: D209.6 (CKO), D210.3 (CKI)
unnamed: D210.1 (SDO), D211.2 (SDI)
unnamed: D210.6 (CKO), D211.3 (CKI)
unnamed: D211.1 (SDO), D212.2 (SDI)
unnamed: D211.6 (CKO), D212.3 (CKI)
unnamed: D212.1 (SDO), D213.2 (SDI)
unnamed: D212.6 (CKO), D213.3 (CKI)
unnamed: D213.1 (SDO), D214.2 (SDI)
unnamed: D213.6 (CKO), D214.3 (CKI)
unnamed: D214.1 (SDO), D215.2 (SDI)
unnamed: D214.6 (CKO), D215.3 (CKI)
unnamed: D215.1 (SDO), D216.2 (SDI)
unnamed: D215.6 (CKO), D216.3 (CKI)
unnamed: D216.1 (SDO), D217.2 (SDI)
unnamed: D216.6 (CKO), D217.3 (CKI)
unnamed: D217.1 (SDO), D218.2 (SDI)
unnamed: D217.6 (CKO), D218.3 (CKI)
unnamed: D218.1 (SDO), D219.2 (SDI)
unnamed: D218.6 (CKO), D219.3 (CKI)
unnamed: D219.1 (SDO), D220.2 (SDI)
unnamed: D219.6 (CKO), D220.3 (CKI)
unnamed: D220.1 (SDO), D221.2 (SDI)
unnamed: D220.6 (CKO), D221.3 (CKI)
unnamed: D221.1 (SDO), D222.2 (SDI)
unnamed: D221.6 (CKO), D222.3 (CKI)
unnamed: D222.1 (SDO), D223.2 (SDI)
unnamed: D222.6 (CKO), D223.3 (CKI)
unnamed: D223.1 (SDO), D224.2 (SDI)
unnamed: D223.6 (CKO), D224.3 (CKI)
unnamed: D224.1 (SDO), D225.2 (SDI)
unnamed: D224.6 (CKO), D225.3 (CKI)
unnamed: D225.1 (SDO), D226.2 (SDI)
unnamed: D225.6 (CKO), D226.3 (CKI)
unnamed: D226.1 (SDO), D227.2 (SDI)
unnamed: D226.6 (CKO), D227.3 (CKI)
unnamed: D227.1 (SDO), D228.2 (SDI)
unnamed: D227.6 (CKO), D228.3 (CKI)
unnamed: D228.1 (SDO), D229.2 (SDI)
unnamed: D228.6 (CKO), D229.3 (CKI)
unnamed: D229.1 (SDO), D230.2 (SDI)
unnamed: D229.6 (CKO), D230.3 (CKI)
unnamed: D230.1 (SDO), D231.2 (SDI)
unnamed: D230.6 (CKO), D231.3 (CKI)
unnamed: D231.1 (SDO), D232.2 (SDI)
unnamed: D231.6 (CKO), D232.3 (CKI)
unnamed: D232.1 (SDO), D233.2 (SDI)
unnamed: D232.6 (CKO), D233.3 (CKI)
unnamed: D233.1 (SDO), D234.2 (SDI)
unnamed: D233.6 (CKO), D234.3 (CKI)
unnamed: D234.1 (SDO), D235.2 (SDI)
unnamed: D234.6 (CKO), D235.3 (CKI)
unnamed: D235.1 (SDO), D236.2 (SDI)
unnamed: D235.6 (CKO), D236.3 (CKI)
unnamed: D236.1 (SDO), D237.2 (SDI)
unnamed: D236.6 (CKO), D237.3 (CKI)
unnamed: D237.1 (SDO), D238.2 (SDI)
unnamed: D237.6 (CKO), D238.3 (CKI)
unnamed: D238.1 (SDO), D239.2 (SDI)
unnamed: D238.6 (CKO), D239.3 (CKI)
unnamed: D239.1 (SDO), D240.2 (SDI)
unnamed: D239.6 (CKO), D240.3 (CKI)
unnamed: D240.1 (SDO), D241.2 (SDI)
unnamed: D240.6 (CKO), D241.3 (CKI)
unnamed: D241.1 (SDO), D242.2 (SDI)
unnamed: D241.6 (CKO), D242.3 (CKI)
VCC: C1.1, C2.1, D1.5 (VCC), D2.5 (VCC), D3.5 (VCC), D4.5 (VCC), D5.5 (VCC), D6.5 (VCC), D7.5 (VCC), D8.5 (VCC), D9.5 (VCC), D10.5 (VCC), D11.5 (VCC), D12.5 (VCC), D13.5 (VCC), D14.5 (VCC), D15.5 (VCC), D16.5 (VCC), D17.5 (VCC), D18.5 (VCC), D19.5 (VCC), D20.5 (VCC), D21.5 (VCC), D22.5 (VCC), D23.5 (VCC), D24.5 (VCC), D25.5 (VCC), D26.5 (VCC), D27.5 (VCC), D28.5 (VCC), D29.5 (VCC), D30.5 (VCC), D31.5 (VCC), D32.5 (VCC), D33.5 (VCC), D34.5 (VCC), D35.5 (VCC), D36.5 (VCC), D37.5 (VCC), D38.5 (VCC), D39.5 (VCC), D40.5 (VCC), D41.5 (VCC), D42.5 (VCC), D43.5 (VCC), D44.5 (VCC), D45.5 (VCC), D46.5 (VCC), D47.5 (VCC), D48.5 (VCC), D49.5 (VCC), D50.5 (VCC), D51.5 (VCC), D52.5 (VCC), D53.5 (VCC), D54.5 (VCC), D55.5 (VCC), D56.5 (VCC), D57.5 (VCC), D58.5 (VCC), D59.5 (VCC), D60.5 (VCC), D61.5 (VCC), D62.5 (VCC), D63.5 (VCC), D64.5 (VCC), D65.5 (VCC), D66.5 (VCC), D67.5 (VCC), D68.5 (VCC), D69.5 (VCC), D70.5 (VCC), D71.5 (VCC), D72.5 (VCC), D73.5 (VCC), D74.5 (VCC), D75.5 (VCC), D76.5 (VCC), D77.5 (VCC), D78.5 (VCC), D79.5 (VCC), D80.5 (VCC), D81.5 (VCC), D82.5 (VCC), D83.5 (VCC), D84.5 (VCC), D85.5 (VCC), D86.5 (VCC), D87.5 (VCC), D88.5 (VCC), D89.5 (VCC), D90.5 (VCC), D91.5 (VCC), D92.5 (VCC), D93.5 (VCC), D94.5 (VCC), D95.5 (VCC), D96.5 (VCC), D97.5 (VCC), D98.5 (VCC), D99.5 (VCC), D100.5 (VCC), D101.5 (VCC), D102.5 (VCC), D103.5 (VCC), D104.5 (VCC), D105.5 (VCC), D106.5 (VCC), D107.5 (VCC), D108.5 (VCC), D109.5 (VCC), D110.5 (VCC), D111.5 (VCC), D112.5 (VCC), D113.5 (VCC), D114.5 (VCC), D115.5 (VCC), D116.5 (VCC), D117.5 (VCC), D118.5 (VCC), D119.5 (VCC), D120.5 (VCC), D121.5 (VCC), D122.5 (VCC), D123.5 (VCC), D124.5 (VCC), D125.5 (VCC), D126.5 (VCC), D127.5 (VCC), D128.5 (VCC), D129.5 (VCC), D130.5 (VCC), D131.5 (VCC), D132.5 (VCC), D133.5 (VCC), D134.5 (VCC), D135.5 (VCC), D136.5 (VCC), D137.5 (VCC), D138.5 (VCC), D139.5 (VCC), D140.5 (VCC), D141.5 (VCC), D142.5 (VCC), D143.5 (VCC), D144.5 (VCC), D145.5 (VCC), D146.5 (VCC), D147.5 (VCC), D148.5 (VCC), D149.5 (VCC), D150.5 (VCC), D151.5 (VCC), D152.5 (VCC), D153.5 (VCC), D154.5 (VCC), D155.5 (VCC), D156.5 (VCC), D157.5 (VCC), D158.5 (VCC), D159.5 (VCC), D160.5 (VCC), D161.5 (VCC), D162.5 (VCC), D163.5 (VCC), D164.5 (VCC), D165.5 (VCC), D166.5 (VCC), D167.5 (VCC), D168.5 (VCC), D169.5 (VCC), D170.5 (VCC), D171.5 (VCC), D172.5 (VCC), D173.5 (VCC), D174.5 (VCC), D175.5 (VCC), D176.5 (VCC), D177.5 (VCC), D178.5 (VCC), D179.5 (VCC), D180.5 (VCC), D181.5 (VCC), D182.5 (VCC), D183.5 (VCC), D184.5 (VCC), D185.5 (VCC), D186.5 (VCC), D187.5 (VCC), D188.5 (VCC), D189.5 (VCC), D190.5 (VCC), D191.5 (VCC), D192.5 (VCC), D193.5 (VCC), D194.5 (VCC), D195.5 (VCC), D196.5 (VCC), D197.5 (VCC), D198.5 (VCC), D199.5 (VCC), D200.5 (VCC), D201.5 (VCC), D202.5 (VCC), D203.5 (VCC), D204.5 (VCC), D205.5 (VCC), D206.5 (VCC), D207.5 (VCC), D208.5 (VCC), D209.5 (VCC), D210.5 (VCC), D211.5 (VCC), D212.5 (VCC), D213.5 (VCC), D214.5 (VCC), D215.5 (VCC), D216.5 (VCC), D217.5 (VCC), D218.5 (VCC), D219.5 (VCC), D220.5 (VCC), D221.5 (VCC), D222.5 (VCC), D223.5 (VCC), D224.5 (VCC), D225.5 (VCC), D226.5 (VCC), D227.5 (VCC), D228.5 (VCC), D229.5 (VCC), D230.5 (VCC), D231.5 (VCC), D232.5 (VCC), D233.5 (VCC), D234.5 (VCC), D235.5 (VCC), D236.5 (VCC), D237.5 (VCC), D238.5 (VCC), D239.5 (VCC), D240.5 (VCC), D241.5 (VCC), D242.5 (VCC), J1.2

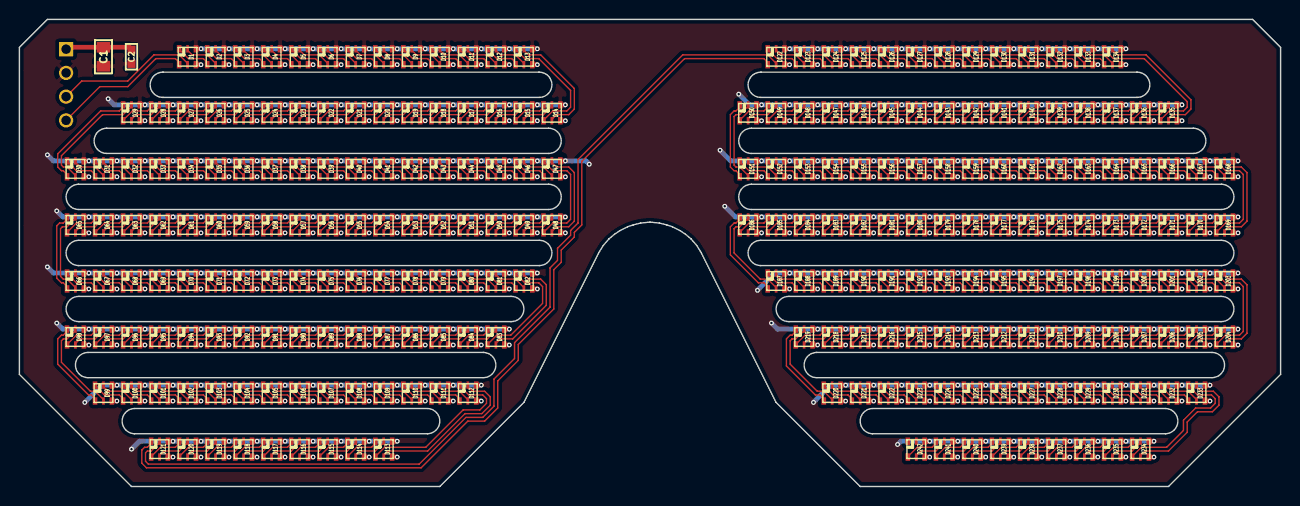
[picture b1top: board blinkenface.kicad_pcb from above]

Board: 2 copper layers, 135.0 x 50.0 mm, 245 parts (1 on the bottom side), 486 nets.

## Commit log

2017-11-18 added gsg-kicad-lib as a submodule
2017-11-18 first revision of hardware design, just the front panel
2017-12-06 fixed APA102-2020 pin order
2017-12-06 GreatFET test script
2017-12-17 reimplemented schematic with skidl
2017-12-17 updated .gitignore for skidl
2017-12-17 Oh, right. Python.
2018-02-08 fixed net names
